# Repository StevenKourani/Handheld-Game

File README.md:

# Handheld Game
A custom-built handheld console powered by an STM32 microcontroller, featuring a 2.8" TFT display, joystick/button controls, and modular game firmware.  
This repository contains both the **hardware design files** (KiCad) and **firmware source code**.

---

## 🔧 Hardware Overview

- **MCU:** STM32F411RE (Nucleo board in development, custom PCB for production)  
- **Display:** ILI9341 2.8" TFT LCD (SPI)  
- **Controls:** Analog joystick + push buttons  
- **Audio:** Passive buzzer with PWM for sound effects  
- **Power:**
  - Li-ion battery with power management
  - **Buck-boost converter** allows the battery to be used both above and below 3.3V
  - USB-C charging option
  - Current switch for allowing fast charging of the battery
  - Power switch (on/off)
  - LED indicators for low battery and fully charged states  
- **PCB Design:** Created in KiCad 9, includes Gerbers, BOM, and KiCad project files.
- **Status:** Board was fabricated, and the power system was tested successfully.

---

## 💻 Firmware Overview

- Written in **C** using STM32 HAL drivers.
- Includes:
  - LCD graphics rendering
  - Joystick input via ADC
  - Button input with debouncing
  - Passive buzzer using PWM for sound effects
  - Game logic (Breakout, menu system, sound effects)
- Developed in **STM32CubeIDE**.
- Board is flashed using **Serial Wire Debug (SWD)**.
- Two additional onboard peripherals are available: **USART** and **I²C**.
- **Important:**  
  The code works, but you must update all pin numbers and peripheral configurations to match your own board.  
  In the first PCB revision, firmware flashing on the custom board was not possible due to a missing capacitor on the **VCAP** pin, preventing the CPU from running.  
  The current version in this repository has been updated to include this capacitor.

---

## 🎮 Game Details

- **Breakout** is implemented and functional but currently missing:
  - Pause function
  - Game Over function  
- Work is in progress to complete these features and to add more games, including **Snake**.

---

## 🚀 Getting Started

### 1. Hardware
- Open `Kicad/` in **KiCad 9.0**.
- Gerber and BOM files are available in `Gerbers/` and `Fabrication/` for PCB fabrication.

### 2. Firmware
- Open the `Inc/` and `Src/` folders in **STM32CubeIDE**.
- Connect your STM32 board (e.g., Nucleo-F411RE or your custom PCB).
- Compile and flash the firmware using **SWD**.

---

## 🤝 Contributing

This is my **first time designing and fabricating a PCB**.  
If anyone has improvements for the KiCad design or firmware, please:
- **Fork** this repository
- Make your changes
- Submit a **Pull Request** so the improvements can be reviewed and merged.

I would love to know if this updated version of the handheld works for you!

---

## 📜 License

This project is licensed under the **MIT License** (see `LICENSE` file).

---

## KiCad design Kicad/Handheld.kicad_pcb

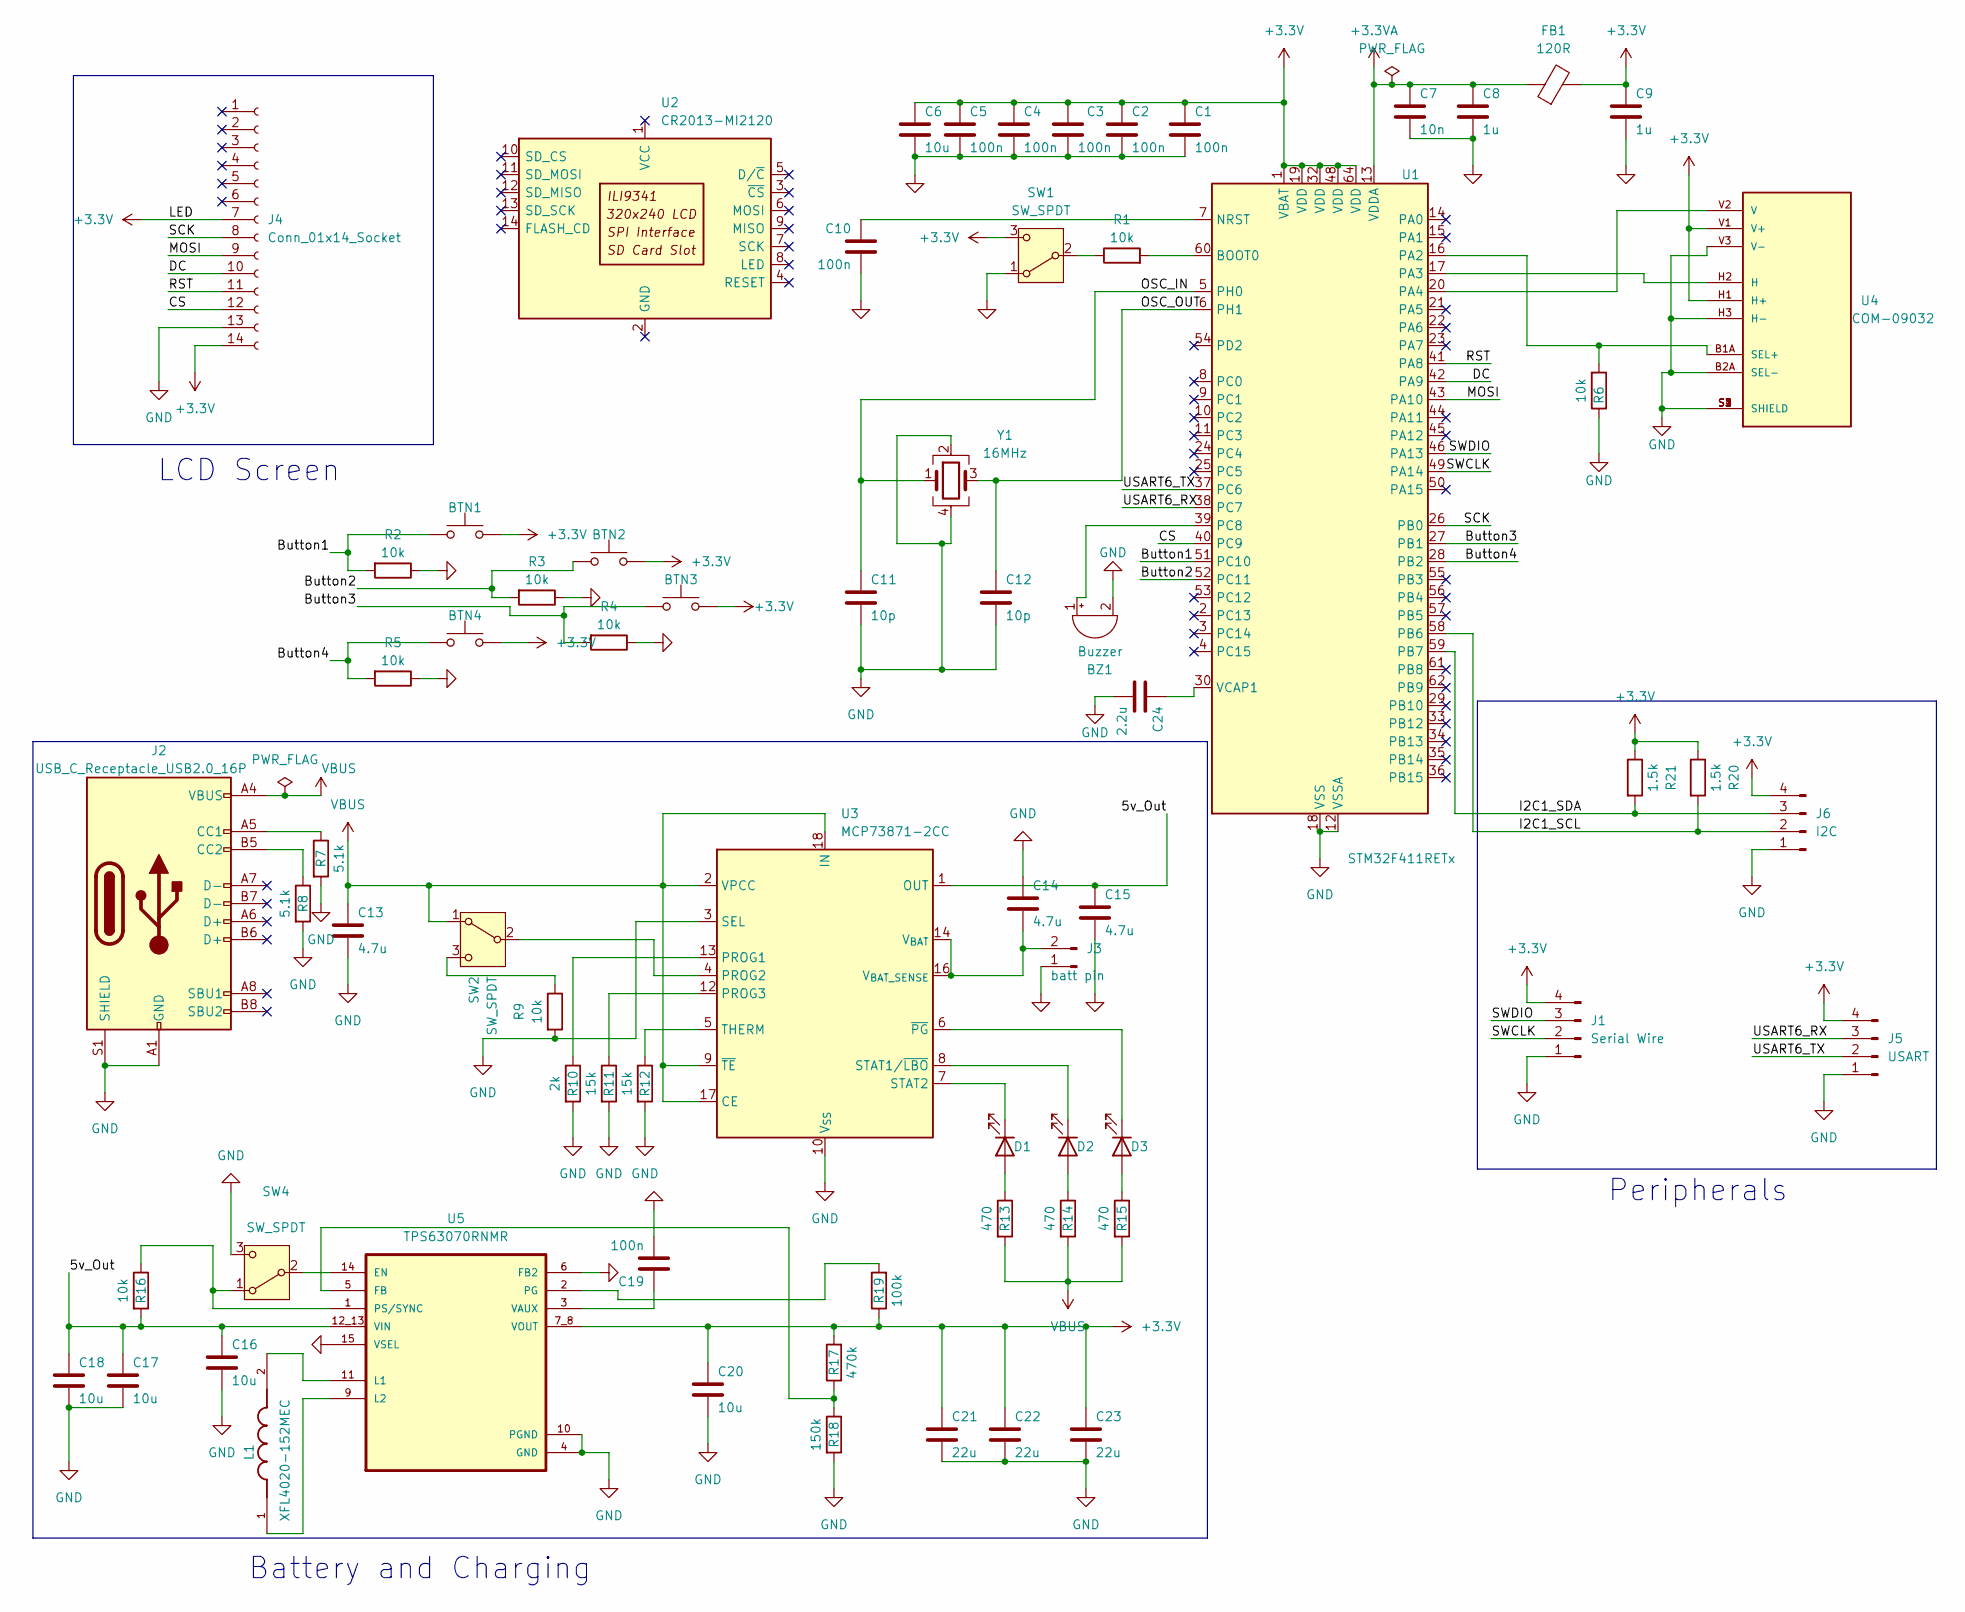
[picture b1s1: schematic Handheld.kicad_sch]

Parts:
BTN1, BTN2, BTN3, BTN4: SW_PUSH_6mm_H4.3mm
BZ1: Buzzer; Buzzer_TDK_PS1240P02BT_D12.2mm_H6.5mm
C1, C2, C3, C4, C5, C10: 100n; C_0402_1005Metric; LCSC C1525
C6, C16, C20: 10u; C_0603_1608Metric; LCSC C96446
C7: 10n; C_0402_1005Metric; LCSC C15195
C8, C9: 1u; C_0402_1005Metric; LCSC C52923
C11, C12: 10p; C_0402_1005Metric; LCSC C32949
C13, C14, C15: 4.7u; C_0603_1608Metric; LCSC C1705
C17, C18: 10u; C_0805_2012Metric; LCSC C694191
C19: 100n; C_0402_1005Metric; LCSC C105883
C21, C22, C23: 22u; C_0805_2012Metric; LCSC C258782
C24: 2.2u; C_0402_1005Metric; LCSC C12530
D1: LED_0603_1608Metric; LCSC C12624
D2: LED_0603_1608Metric; LCSC C2286
D3: LED_0603_1608Metric; LCSC C2290
FB1: 120R; L_0603_1608Metric; LCSC C1002
J1: Serial Wire; PinHeader_1x04_P2.54mm_Vertical
J2: USB_C_Receptacle_USB2.0_16P; USB_C_Receptacle_GCT_USB4105-xx-A_16P_TopMnt_Horizontal; LCSC C5342196
J3: batt pin; JST_PH_B2B-PH-K_1x02_P2.00mm_Vertical
J4: Conn_01x14_Socket; PinSocket_1x14_P2.54mm_Vertical
J5: USART; PinHeader_1x04_P2.54mm_Vertical
J6: I2C; PinHeader_1x04_P2.54mm_Vertical
L1: XFL4020-152MEC; IND_XFL4020-152MEC; PARTREV 11/02/18; LCSC C3033018
R1, R2, R3, R4, R5, R6, R9, R16: 10k; R_0402_1005Metric; LCSC C25744
R7, R8: 5.1k; R_0402_1005Metric; LCSC C25905
R10: 2k; R_0402_1005Metric; LCSC C4109
R11, R12: 15k; R_0402_1005Metric; LCSC C25756
R13, R14, R15: 470; R_0402_1005Metric; LCSC C25117
R17: 470k; R_0402_1005Metric; LCSC C17709
R18: 150k; R_0402_1005Metric; LCSC C17470
R19: 100k; R_0402_1005Metric; LCSC C25741
R20, R21: 1.5k; R_0402_1005Metric; LCSC C25867
SW1, SW4: SW_SPDT; SW_SPDT_PCM12; LCSC C221841
SW2: SW_SPDT; SW_SPDT_PCM12; LCSC C273395
U1: STM32F411RETx; LQFP-64_10x10mm_P0.5mm; LCSC C94355
U2: CR2013-MI2120
U3: MCP73871-2CC; QFN-20-1EP_4x4mm_P0.5mm_EP2.5x2.5mm; LCSC C5121473
U4: COM-09032; XDCR_COM-09032; PARTREV N/A
U5: TPS63070RNMR; VREG_TPS63070RNMR; LCSC C109322
Y1: 16MHz; Crystal_SMD_SeikoEpson_TSX3225-4Pin_3.2x2.5mm; LCSC C112972

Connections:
+3.3V: BTN1.1, BTN2.2, BTN3.2, BTN4.2, C1.1, C2.1, C3.1, C4.1, C5.1, C6.1, C9.1, C20.1, C21.1, C22.1, C23.1, FB1.2, J1.4, J4.7, J4.14, J5.4, J6.4, R17.2, R19.1, R20.1, R21.1, SW1.3 (C), U1.1 (VBAT), U1.19 (VDD), U1.32 (VDD), U1.48 (VDD), U1.64 (VDD), U4.H1 (H+), U4.V1 (V+), U5.7_8 (VOUT)
+3.3VA: C7.1, C8.1, FB1.1, U1.13 (VDDA)
/5v_Out: C15.1, C16.1, C17.1, C18.1, R16.2, U3.1 (OUT), U3.20 (OUT), U5.12_13 (VIN)
/Button1: BTN1.2, R2.2, U1.51 (PC10)
/Button2: BTN2.1, R3.2, U1.52 (PC11)
/Button3: BTN3.1, R4.2, U1.27 (PB1)
/Button4: BTN4.1, R5.2, U1.28 (PB2)
/CS: J4.12, U1.40 (PC9)
/DC: J4.10, U1.42 (PA9)
/I2C1_SCL: J6.2, R20.2, U1.58 (PB6)
/I2C1_SDA: J6.3, R21.2, U1.59 (PB7)
/MOSI: J4.9, U1.43 (PA10)
/OSC_IN: C11.1, U1.5 (PH0), Y1.1
/OSC_OUT: C12.1, U1.6 (PH1), Y1.3
/RST: J4.11, U1.41 (PA8)
/SCK: J4.8, U1.26 (PB0)
/SWCLK: J1.2, U1.49 (PA14)
/SWDIO: J1.3, U1.46 (PA13)
/USART6_RX: J5.3, U1.38 (PC7)
/USART6_TX: J5.2, U1.37 (PC6)
GND: BZ1.2 (-), C1.2, C2.2, C3.2, C4.2, C5.2, C6.2, C7.2, C8.2, C9.2, C10.2, C11.2, C12.2, C13.2, C14.1, C15.2, C16.2, C17.2, C18.2, C19.2, C20.2, C21.2, C22.2, C23.2, C24.2, J1.1, J2.A1 (GND), J2.A12 (GND), J2.B1 (GND), J2.B12 (GND), J2.S1 (SHIELD), J3.1, J4.13, J5.1, J6.1, R2.1, R3.1, R4.1, R5.1, R6.1, R7.2, R8.2, R9.2, R10.2, R11.2, R12.2, R18.2, SW1.1 (A), SW4.3 (C), U1.12 (VSSA), U1.18 (VSS), U1.31 (VSS), U1.47 (VSS), U1.63 (VSS), U3.3 (SEL), U3.10 (V_{SS}), U3.11 (V_{SS}), U3.21 (V_{SS}), U4.B2A (SEL-), U4.H3 (H-), U4.S1 (SHIELD), U4.S2 (SHIELD), U4.S3 (SHIELD), U4.S4 (SHIELD), U4.V3 (V-), U5.4 (GND), U5.6 (FB2), U5.10 (PGND), U5.15 (VSEL), Y1.2, Y1.4
unnamed: BZ1.1 (+), U1.39 (PC8)
unnamed: D1.2 (A), R13.1
unnamed: D1.1 (K), U3.7 (STAT2)
unnamed: D2.2 (A), R14.1
unnamed: D2.1 (K), U3.8 (STAT1/~LBO)
unnamed: D3.2 (A), R15.1
unnamed: D3.1 (K), U3.6 (~PG)
unnamed: J2.A5 (CC1), R7.1
unnamed: J2.B5 (CC2), R8.1
unnamed: C14.2, J3.2, U3.14 (V_{BAT}), U3.15 (V_{BAT}), U3.16 (V_{BAT_SENSE})
unnamed: R1.1, SW1.2 (B)
unnamed: SW2.2 (B), U3.4 (PROG2)
unnamed: R9.1, SW2.3 (C)
unnamed: R16.1, SW4.1 (A), U5.1 (PS/SYNC)
unnamed: SW4.2 (B), U5.14 (EN)
unnamed: R1.2, U1.60 (BOOT0)
unnamed: C10.1, U1.7 (NRST)
unnamed: R6.2, U1.16 (PA2), U4.B1A (SEL+)
unnamed: U1.17 (PA3), U4.H2 (H)
unnamed: U1.20 (PA4), U4.V2 (V)
unnamed: C24.1, U1.30 (VCAP1)
unnamed: R10.1, U3.13 (PROG1)
unnamed: R11.1, U3.12 (PROG3)
unnamed: R12.1, U3.5 (THERM)
unnamed: R17.1, R18.1, U5.5 (FB)
unnamed: L1.2, U5.11 (L1)
unnamed: L1.1, U5.9 (L2)
unnamed: R19.2, U5.2 (PG)
unnamed: C19.1, U5.3 (VAUX)
VBUS: C13.1, J2.A4 (VBUS), J2.A9 (VBUS), J2.B4 (VBUS), J2.B9 (VBUS), R13.2, R14.2, R15.2, SW2.1 (A), U3.2 (VPCC), U3.9 (~TE), U3.17 (CE), U3.18 (IN), U3.19 (IN)

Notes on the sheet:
Battery and Charging
Peripherals
LCD Screen

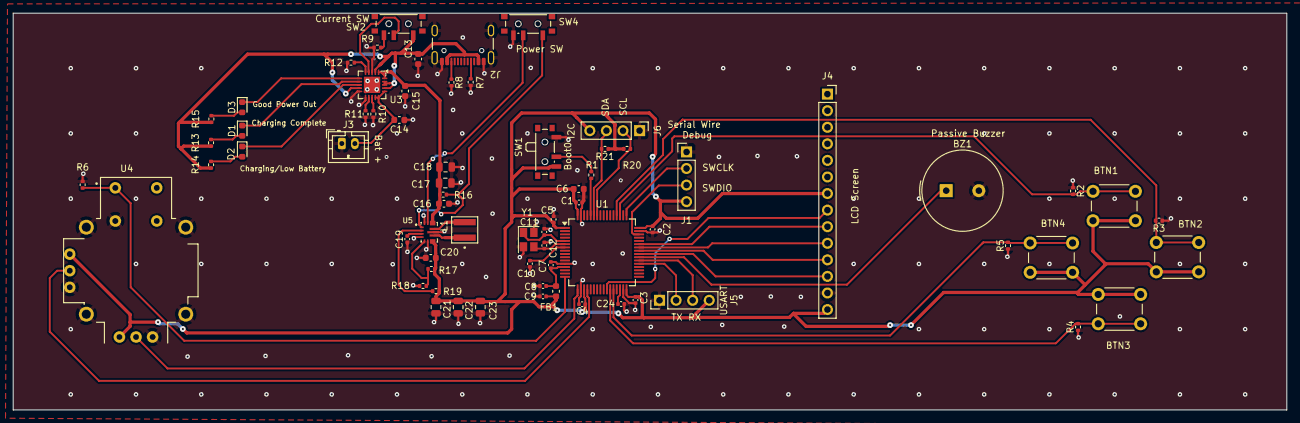
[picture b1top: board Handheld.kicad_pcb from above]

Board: 2 copper layers, 195.2 x 60.8 mm, 69 parts (0 on the bottom side), 51 nets.

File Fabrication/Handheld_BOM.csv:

Comment,Designator,Footprint,LCSC PN
"C1,C2,C3,C4,C5,C10",100n,Capacitor_SMD:C_0402_1005Metric,C1525
C19,100n,Capacitor_SMD:C_0402_1005Metric,C105883
"C17,C18",10u,Capacitor_SMD:C_0805_2012Metric,C694191
"C6,C16,C20",10u,Capacitor_SMD:C_0603_1608Metric,C96446
C7,10n,Capacitor_SMD:C_0402_1005Metric,C15195
"C8,C9",1u,Capacitor_SMD:C_0402_1005Metric,C52923
"C11,C12",10p,Capacitor_SMD:C_0402_1005Metric, C32949
"C13,C14,C15",4.7u,Capacitor_SMD:C_0603_1608Metric, C1705
"C21,C22,C23",22u,Capacitor_SMD:C_0805_2012Metric,C258782
C24,2.2u,Capacitor_SMD:C_0402_1005Metric,C12530
D1,~,LED_SMD:LED_0603_1608Metric,C12624 
D2,~,LED_SMD:LED_0603_1608Metric, C2286
D3,~,LED_SMD:LED_0603_1608Metric,C2290
FB1,120R,Inductor_SMD:L_0603_1608Metric, C1002
J2,USB_C_Receptacle_USB2.0_16P,Connector_USB:USB_C_Receptacle_GCT_USB4105-xx-A_16P_TopMnt_Horizontal,C5342196
L1,XFL4020-152MEC,XFL4020-152MEC:IND_XFL4020-152MEC,C3033018
"R1,R2,R3,R4,R5,R6,R9,R16",10k,Resistor_SMD:R_0402_1005Metric,C25744
"R7,R8",5.1k,Resistor_SMD:R_0402_1005Metric, C25905
R10,2k,Resistor_SMD:R_0402_1005Metric,C4109
"R11,R12",15k,Resistor_SMD:R_0402_1005Metric,C25756
"R13,R14,R15",470,Resistor_SMD:R_0402_1005Metric, C25117
R17,470k,Resistor_SMD:R_0402_1005Metric,C17709
R18,150k,Resistor_SMD:R_0402_1005Metric,C17470
R19,100k,Resistor_SMD:R_0402_1005Metric, C25741
"R20,R21",1.5k,Resistor_SMD:R_0402_1005Metric, C25867
"SW1,SW2,SW4",SW_SPDT,Button_Switch_SMD:SW_SPDT_PCM12, C221841
U1,STM32F411RETx,Package_QFP:LQFP-64_10x10mm_P0.5mm, C94355
U3,MCP73871-2CC,Package_DFN_QFN:QFN-20-1EP_4x4mm_P0.5mm_EP2.5x2.5mm,C5121473
U5,TPS63070RNMR,TPS63070RNMR:VREG_TPS63070RNMR,C109322
Y1,16MHz,Crystal:Crystal_SMD_SeikoEpson_TSX3225-4Pin_3.2x2.5mm, C112972
